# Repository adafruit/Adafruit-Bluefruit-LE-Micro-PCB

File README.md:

## Adafruit Bluefruit LE Micro PCB (Discontinued)
<a href="http://www.adafruit.com/products/2661"><br/>
See the part listing in the Adafruit shop</a>

DISCONTINUED
Check out the [Adafruit Feather 32u4 Bluefruit LE](https://www.adafruit.com/products/2829), it's an awesome upgrade!

PCB files for Adafruit Bluefruit LE Micro. Format is EagleCAD.
- https://www.adafruit.com/product/2661

### License

Adafruit invests time and resources providing this open source design, please support Adafruit and open-source hardware by purchasing products from [Adafruit](https://www.adafruit.com)!

All text above must be included in any redistribution

Designed by Limor Fried/Ladyada for Adafruit Industries.
Creative Commons Attribution/Share-Alike, all text above must be included in any redistribution. 
See license.txt for additional information.

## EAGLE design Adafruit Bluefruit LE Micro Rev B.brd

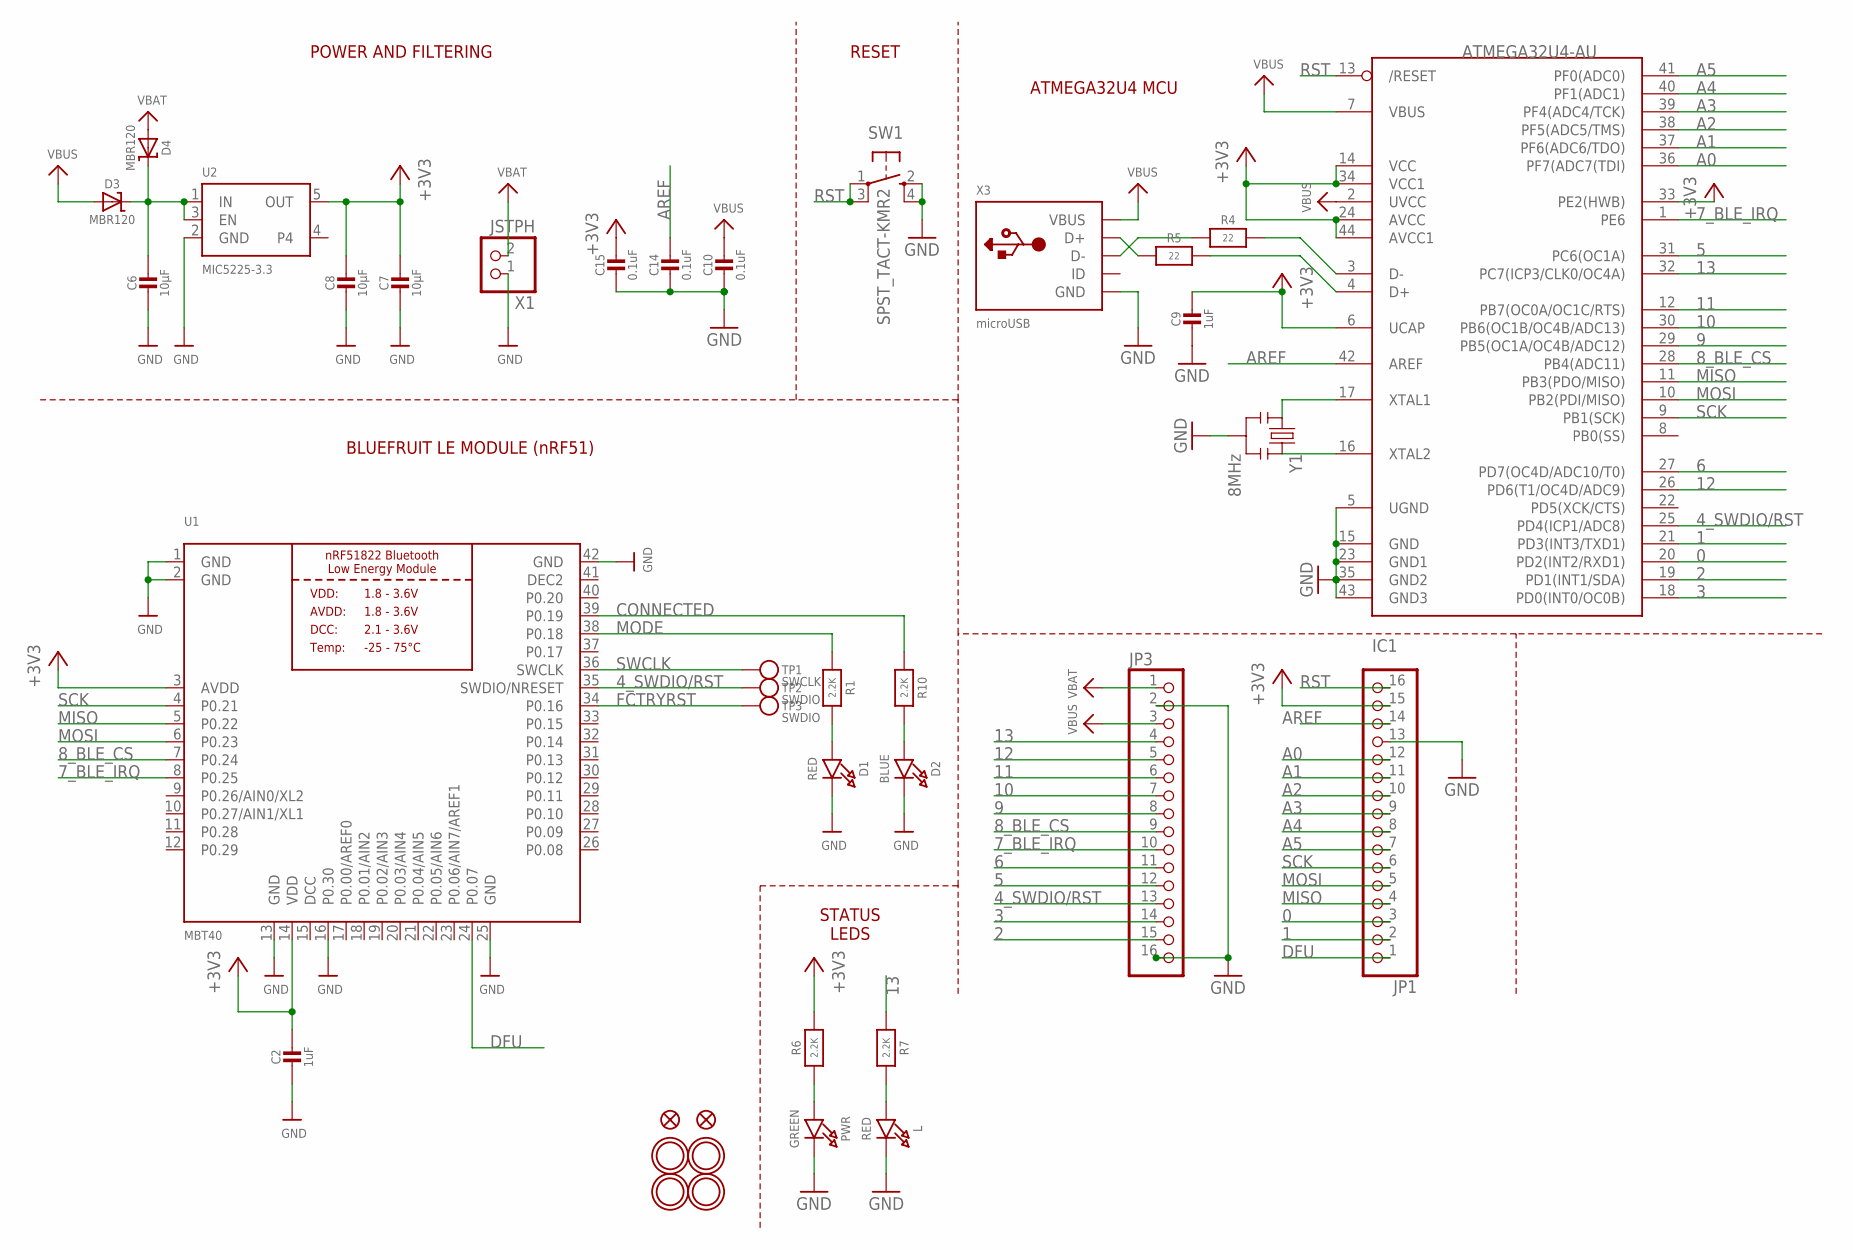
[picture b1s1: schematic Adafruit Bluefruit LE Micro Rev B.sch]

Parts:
C2, C9: 1uF; 0805-NO
C6: 10µF; _0805MP
C7, C8: 10µF; 0805-NO
C10: 0.1uF; 0805_10MGAP
C14, C15: 0.1uF; 0805-NO
D1: RED; CHIPLED_0805_NOOUTLINE
D2: BLUE; CHIPLED_0805_NOOUTLINE
D3, D4: MBR120; SOD-123
IC1: ATMEGA32U4-AU; TQFP44
JP1, JP3: HEADER-1X16ROUND; 1X16_ROUND
L: RED; CHIPLED_0805_NOOUTLINE
PWR: GREEN; CHIPLED_0805_NOOUTLINE
R1, R6, R7, R10: 2.2K; 0805-NO
R4, R5: 22; 0805-NO
SW1: SPST_TACT-KMR2; KMR2
TP1: SWCLK; PAD-1.5X2.0
TP2, TP3: SWDIO; PAD-1.5X2.0
U1: MBT40; BLE_MODULE_RAYTAC_MDBT40
U2: MIC5225-3.3; SOT23-5
U$6, U$24, U$31, U$32: MOUNTINGHOLE2.5; MOUNTINGHOLE_2.5_PLATED
U$34, U$35: FIDUCIAL""; FIDUCIAL_1MM
X1: JSTPH; JSTPH2
X3: microUSB; 4UCONN_20329
Y1: 8MHz; RESONATOR-SMD

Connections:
0: IC1.20 (PD2(INT2/RXD1)), JP1.3
1: IC1.21 (PD3(INT3/TXD1)), JP1.2
2: IC1.19 (PD1(INT1/SDA)), JP3.15
3: IC1.18 (PD0(INT0/OC0B)), JP3.14
4_SWDIO/RST: IC1.25 (PD4(ICP1/ADC8)), JP3.13, TP2.P$1, U1.35 (SWDIO/NRESET)
5: IC1.31 (PC6(OC1A)), JP3.12
6: IC1.27 (PD7(OC4D/ADC10/T0)), JP3.11
7_BLE_IRQ: IC1.1 (PE6), JP3.10, U1.8 (P0.25)
8_BLE_CS: IC1.28 (PB4(ADC11)), JP3.9, U1.7 (P0.24)
9: IC1.29 (PB5(OC1A/OC4B/ADC12)), JP3.8
10: IC1.30 (PB6(OC1B/OC4B/ADC13)), JP3.7
11: IC1.12 (PB7(OC0A/OC1C/RTS)), JP3.6
12: IC1.26 (PD6(T1/OC4D/ADC9)), JP3.5
13: IC1.32 (PC7(ICP3/CLK0/OC4A)), JP3.4, R7.1
+3V3: C2.1, C7.1, C8.1, C9.1, C15.1, IC1.6 (UCAP), IC1.14 (VCC), IC1.24 (AVCC), IC1.33 (PE2(HWB)), IC1.34 (VCC1), IC1.44 (AVCC1), JP1.15, R6.2, U1.3 (AVDD), U1.14 (VDD), U2.5 (OUT)
A0: IC1.36 (PF7(ADC7(TDI)), JP1.12
A1: IC1.37 (PF6(ADC6/TDO)), JP1.11
A2: IC1.38 (PF5(ADC5/TMS)), JP1.10
A3: IC1.39 (PF4(ADC4/TCK)), JP1.9
A4: IC1.40 (PF1(ADC1)), JP1.8
A5: IC1.41 (PF0(ADC0)), JP1.7
AREF: C14.1, IC1.42 (AREF), JP1.14
CONNECTED: R10.1, U1.39 (P0.19)
DCC: U1.15 (DCC)
DEC2: U1.41 (DEC2)
DFU: JP1.1, U1.24 (P0.07)
FCTRYRST: TP3.P$1, U1.34 (P0.16)
GND: C2.2, C6.2, C7.2, C8.2, C9.2, C10.2, C14.2, C15.2, D1.C, D2.C, IC1.5 (UGND), IC1.15 (GND), IC1.23 (GND1), IC1.35 (GND2), IC1.43 (GND3), JP1.13, JP3.2, JP3.16, L.C, PWR.C, SW1.2 (S), SW1.4 (S1), U1.1 (GND), U1.2 (GND), U1.13 (GND), U1.16 (P0.30), U1.25 (GND), U1.42 (GND), U2.2 (GND), X1.1, X3.BASE@1 (GND), X3.BASE@2 (GND), X3.GND, X3.SPRT@1 (GND), X3.SPRT@2 (GND), X3.SPRT@3 (GND), X3.SPRT@4 (GND), Y1.2
MISO: IC1.11 (PB3(PDO/MISO)), JP1.4, U1.5 (P0.22)
MODE: R1.1, U1.38 (P0.18)
MOSI: IC1.10 (PB2(PDI/MISO)), JP1.5, U1.6 (P0.23)
unnamed: L.A, R7.2
unnamed: D1.A, R1.2
unnamed: D2.A, R10.2
unnamed: IC1.3 (D-), R4.2
unnamed: IC1.4 (D+), R5.2
unnamed: IC1.16 (XTAL2), Y1.3
unnamed: IC1.17 (XTAL1), Y1.1
unnamed: PWR.A, R6.1
unnamed: R5.1, X3.D+
unnamed: R4.1, X3.D-
unnamed: C6.1, D3.C, D4.C, U2.1 (IN), U2.3 (EN)
RST: IC1.13 (/RESET), JP1.16, SW1.1, SW1.3 (P1)
SCK: IC1.9 (PB1(SCK)), JP1.6, U1.4 (P0.21)
SWCLK: TP1.P$1, U1.36 (SWCLK)
VBAT: D4.A, JP3.1, X1.2
VBUS: C10.1, D3.A, IC1.2 (UVCC), IC1.7 (VBUS), JP3.3, X3.VBUS

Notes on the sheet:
POWER AND FILTERING
BLUEFRUIT LE MODULE (nRF51)
RESET
ATMEGA32U4 MCU
STATUS LEDS

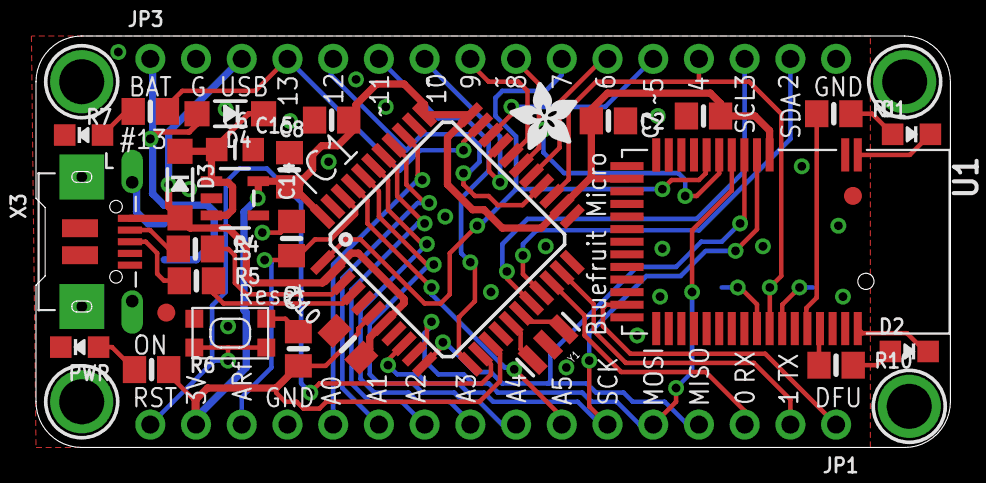
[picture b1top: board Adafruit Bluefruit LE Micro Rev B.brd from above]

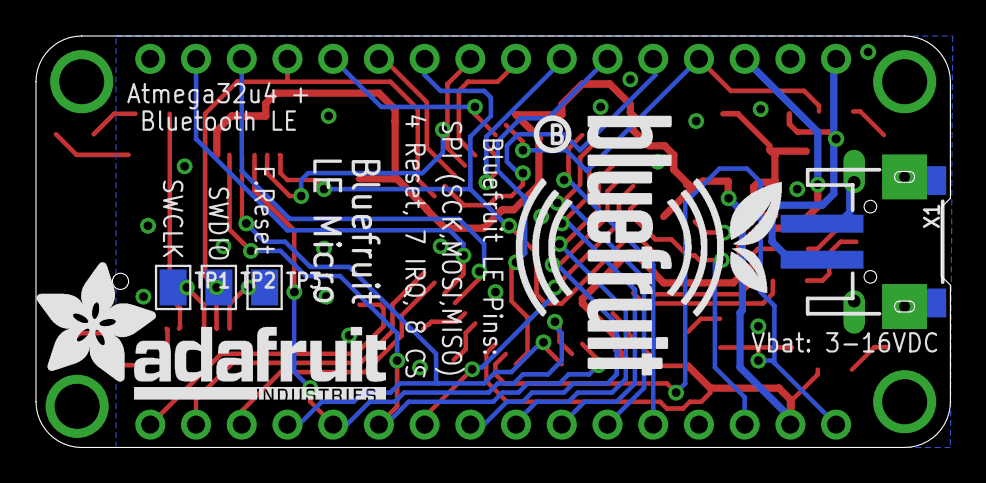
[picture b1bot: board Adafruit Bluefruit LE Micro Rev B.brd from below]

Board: 2 copper layers, 50.8 x 22.9 mm, 42 parts (7 on the bottom side), 45 nets.

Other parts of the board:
U$7: ADAFRUIT_3.5MM
U$9: ADAFRUIT_TEXT_20MM
U$15: BLUEFRUITLOGO_150MM
U$23: PCBFEAT-REV-040

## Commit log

2015-11-30 init

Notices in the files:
parts and their libraries:
microbuilder: This work is placed in the public domain, and may be freely used for commercial and non-commercial work with the following conditions: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
SparkFun: Licensing: CC v3.0 Share-Alike You are welcome to use this library for commercial purposes.
